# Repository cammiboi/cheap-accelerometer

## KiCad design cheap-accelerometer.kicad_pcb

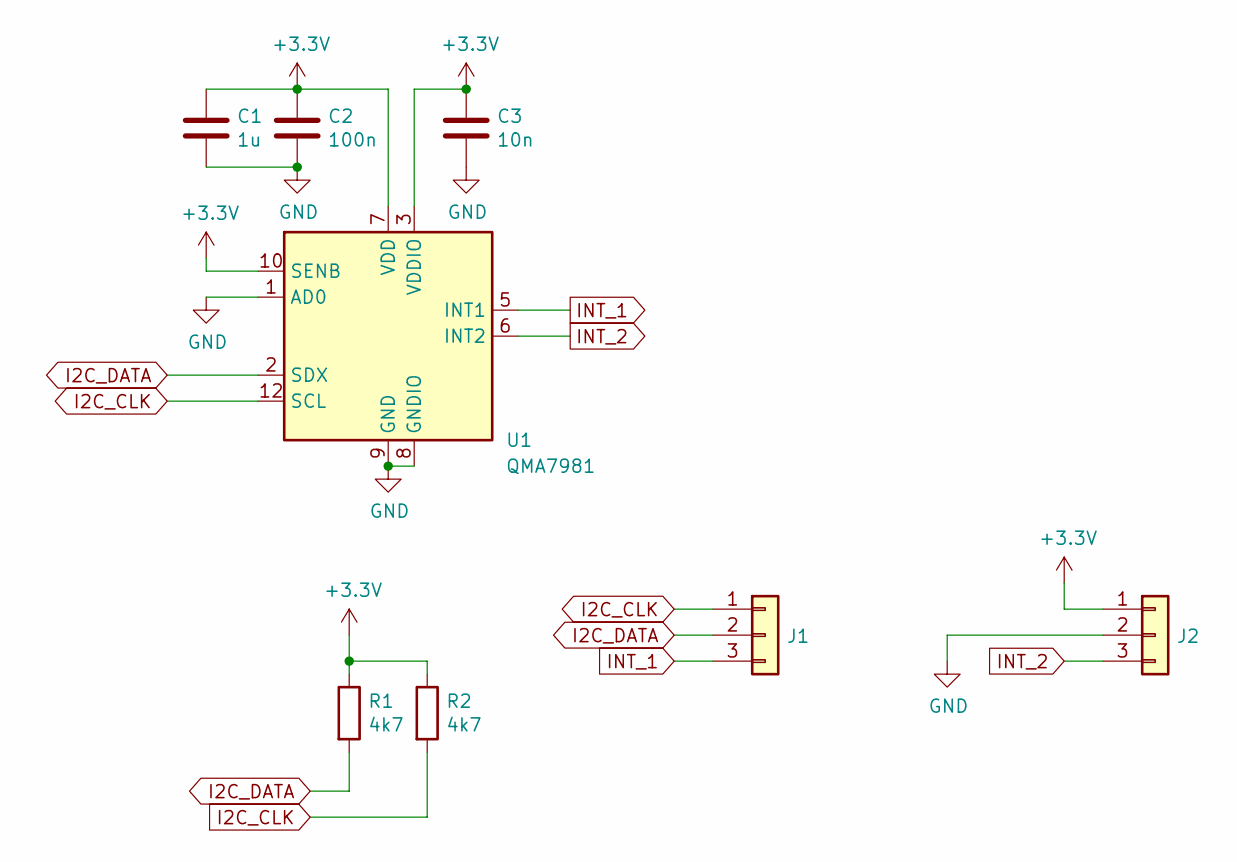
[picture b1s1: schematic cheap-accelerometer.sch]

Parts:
C1: 1u; C_0402_1005Metric; LCSC Part Number C497333
C2: 100n; C_0402_1005Metric; LCSC Part Number C60474
C3: 10n; C_0402_1005Metric; Voltage 100; LCSC Part Number C77439
J1, J2: Conn_01x03; PinHeader_1x03_P2.54mm_Vertical
R1, R2: 4k7; R_0603_1608Metric
U1: QMA7981; LGA-12_2x2mm_P0.5mm

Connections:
+3V3: C1.1, C2.1, C3.1, J2.1, R1.1, R2.1, U1.3 (VDDIO), U1.7 (VDD), U1.10 (SENB)
GND: C1.2, C2.2, C3.2, J2.2, U1.1 (AD0), U1.8 (GNDIO), U1.9 (GND)
I2C_CLK: J1.1, R2.2, U1.12 (SCL)
I2C_DATA: J1.2, R1.2, U1.2 (SDX)
INT_1: J1.3, U1.5 (INT1)
INT_2: J2.3, U1.6 (INT2)

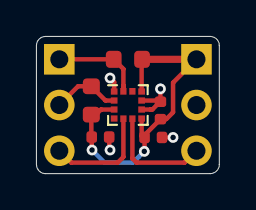
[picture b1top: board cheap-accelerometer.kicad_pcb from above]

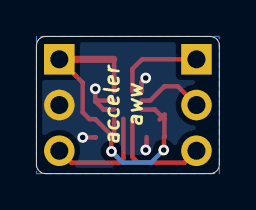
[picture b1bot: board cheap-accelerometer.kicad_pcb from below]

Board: 2 copper layers, 10.2 x 7.6 mm, 8 parts (2 on the bottom side), 6 nets.

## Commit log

2020-12-13 add files for first version
